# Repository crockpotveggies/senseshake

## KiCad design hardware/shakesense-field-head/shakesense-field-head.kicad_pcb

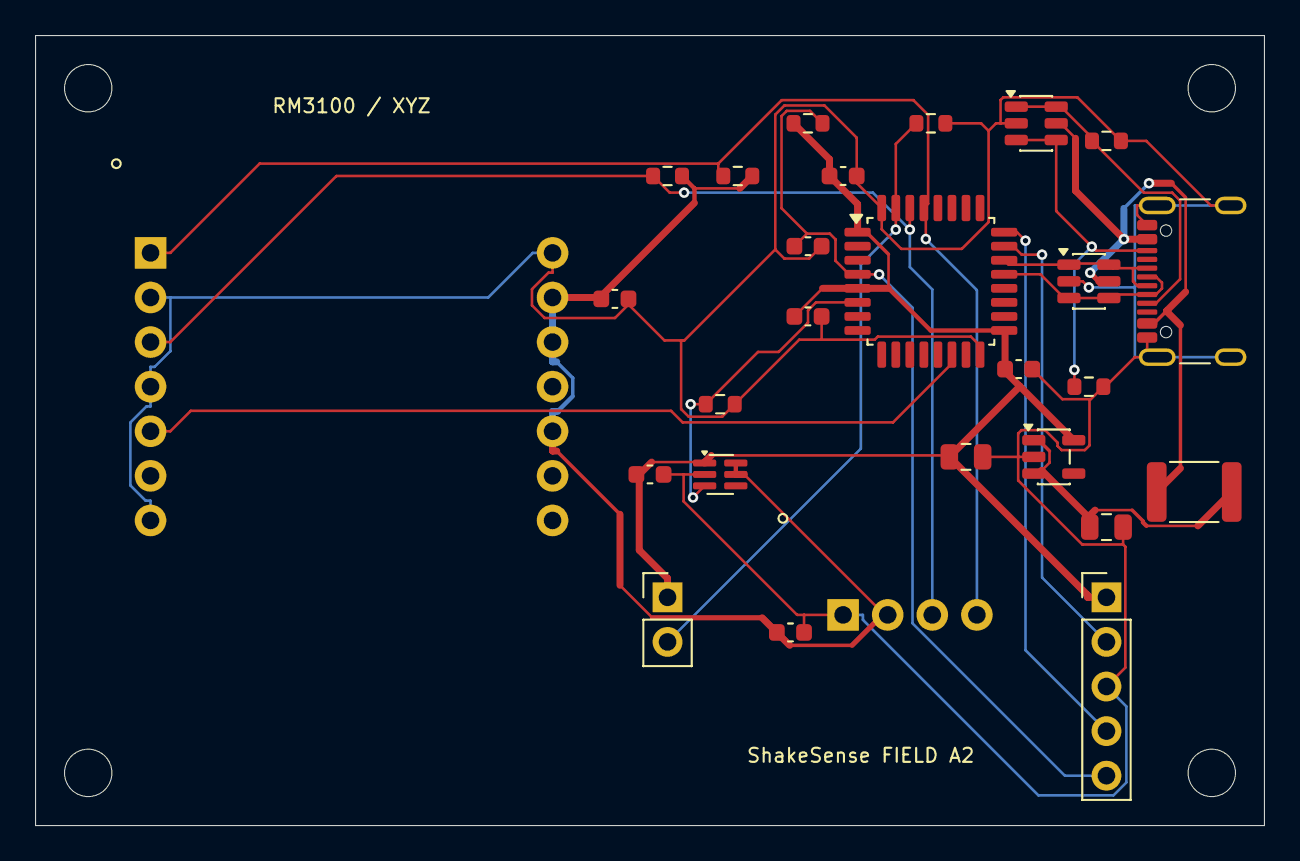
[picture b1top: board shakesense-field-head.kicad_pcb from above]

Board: 4 copper layers, 70.0 x 45.0 mm, 31 parts (0 on the bottom side), 17 nets.

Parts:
C1: 2.2u; Capacitor_SMD__C_0805_2012Metric
C2: 4.7u; Capacitor_SMD__C_0805_2012Metric
C3, C4, C5, C6, C7, C8, C9: 100n; Capacitor_SMD__C_0603_1608Metric
D1, D2: USBLC6-2SC6; Package_TO_SOT_SMD__SOT-23-6
F1: 500mA PTC; Fuse__Fuse_1812_4532Metric
H1, H2, H3, H4: M2.5 NPTH; MountingHole__MountingHole_2.7mm_M2.5
J1: USB-C DEVICE; Connector_USB__USB_C_Receptacle_GCT_USB4105-xx-A_16P_TopMnt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
J2: SWD / 3V3 SENSE; Connector_PinHeader_2.54mm__PinHeader_1x05_P2.54mm_Vertical
J3: BOOT0 jumper; Connector_PinHeader_2.54mm__PinHeader_1x02_P2.54mm_Vertical
R1, R2: 5.1k; Resistor_SMD__R_0603_1608Metric
R3, R4: 10k; Resistor_SMD__R_0603_1608Metric
R5: 100k; Resistor_SMD__R_0603_1608Metric
R7, R8: 4.7k; Resistor_SMD__R_0603_1608Metric
U1: STM32F042K6T6; Package_QFP__LQFP-32_7x7mm_P0.8mm
U2: RM3100 XYZ; ShakeSense__PNI_14190_Module
U3: DLVR-F50D option; ShakeSense__DLVR_E1BS
U4: AP2112K-3.3; Package_TO_SOT_SMD__SOT-23-5
U5: TPS22919; Package_TO_SOT_SMD__SOT-363_SC-70-6

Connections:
BOOT0: J3.2, R4.1, U1.31
GND: C1.2, C2.2, C3.2, C4.2, C5.2, C6.2, C7.2, C8.2, C9.2, D1.2, D2.2, J1.A1, J1.A12, J1.B1, J1.B12, J1.S1, J2.3, R1.2, R2.2, R4.2, R5.2, U1.16, U1.32, U2.2, U2.4, U2.7, U2.14, U3.1, U4.2, U5.2
MAG_DRDY: U1.14, U2.5
NRST: C8.1, J2.5, R3.2, U1.4
SCL: R8.1, U1.29, U2.1, U3.4
SDA: R7.1, U1.30, U2.3, U3.3
SENSOR_EN: R5.1, U1.6, U5.3
SWCLK: J2.4, U1.24
SWDIO: J2.2, U1.23
USB_5V: C1.1, F1.2, U4.1, U4.3
USB_CC1: D2.1, D2.6, J1.A5, R1.1
USB_CC2: D2.3, D2.4, J1.B5, R2.1
USB_DM: D1.3, D1.4, J1.A7, J1.B7, U1.21
USB_DP: D1.1, D1.6, J1.A6, J1.B6, U1.22
USB_VBUS: D1.5, D2.5, F1.1, J1.A4, J1.A9, J1.B4, J1.B9
V3: C2.1, C3.1, C6.1, C7.1, C9.1, J2.1, J3.1, R3.1, U1.1, U1.5, U1.17, U4.5, U5.1
V3_SENSOR: C4.1, C5.1, R7.2, R8.2, U2.10, U2.12, U2.13, U3.2, U5.5, U5.6

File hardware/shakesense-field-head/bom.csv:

Reference,Value,MPN,Footprint,DNP,Note
J1,USB-C DEVICE,USB4105-GF-A,Connector_USB__USB_C_Receptacle_GCT_USB4105-xx-A_16P_TopMnt_Horizontal,False,
R1,5.1k,RC0603FR-075K1L,Resistor_SMD__R_0603_1608Metric,False,
R2,5.1k,RC0603FR-075K1L,Resistor_SMD__R_0603_1608Metric,False,
D1,USBLC6-2SC6,USBLC6-2SC6,Package_TO_SOT_SMD__SOT-23-6,False,
D2,USBLC6-2SC6,USBLC6-2SC6,Package_TO_SOT_SMD__SOT-23-6,False,
F1,500mA PTC,MF-MSMF050-2,Fuse__Fuse_1812_4532Metric,False,
U4,AP2112K-3.3,AP2112K-3.3TRG1,Package_TO_SOT_SMD__SOT-23-5,False,
C1,2.2u,GRM21BR71E225KA73L,Capacitor_SMD__C_0805_2012Metric,False,
C2,4.7u,GRM21BR71A475KA73L,Capacitor_SMD__C_0805_2012Metric,False,
U1,STM32F042K6T6,STM32F042K6T6,Package_QFP__LQFP-32_7x7mm_P0.8mm,False,
C3,100n,GRM188R71H104KA93D,Capacitor_SMD__C_0603_1608Metric,False,
C6,100n,GRM188R71H104KA93D,Capacitor_SMD__C_0603_1608Metric,False,
C7,100n,GRM188R71H104KA93D,Capacitor_SMD__C_0603_1608Metric,False,
C8,100n,GRM188R71H104KA93D,Capacitor_SMD__C_0603_1608Metric,False,
R3,10k,RC0603FR-0710KL,Resistor_SMD__R_0603_1608Metric,False,
R4,10k,RC0603FR-0710KL,Resistor_SMD__R_0603_1608Metric,False,
J2,SWD / 3V3 SENSE,M20-9990545,Connector_PinHeader_2.54mm__PinHeader_1x05_P2.54mm_Vertical,False,Pin 1 is target voltage sense; do not externally power the rail
J3,BOOT0 jumper,EEPROM write enable,Connector_PinHeader_2.54mm__PinHeader_1x02_P2.54mm_Vertical,False,
U5,TPS22919,TPS22919DCKR,Package_TO_SOT_SMD__SOT-363_SC-70-6,False,
R5,100k,RC0603FR-07100KL,Resistor_SMD__R_0603_1608Metric,False,
C9,100n,GRM188R71H104KA93D,Capacitor_SMD__C_0603_1608Metric,False,
R7,4.7k,RC0603FR-074K7L,Resistor_SMD__R_0603_1608Metric,False,
R8,4.7k,RC0603FR-074K7L,Resistor_SMD__R_0603_1608Metric,False,
U2,RM3100 XYZ,PNI 14190,ShakeSense__PNI_14190_Module,False,
C4,100n,GRM188R71H104KA93D,Capacitor_SMD__C_0603_1608Metric,False,
U3,DLVR-F50D option,DLVR-F50D-E1BS-I-NI3F,ShakeSense__DLVR_E1BS,True,
C5,100n,GRM188R71H104KA93D,Capacitor_SMD__C_0603_1608Metric,False,
H1,M2.5 NPTH,M2.5 NPTH,MountingHole__MountingHole_2.7mm_M2.5,False,
H2,M2.5 NPTH,M2.5 NPTH,MountingHole__MountingHole_2.7mm_M2.5,False,
H3,M2.5 NPTH,M2.5 NPTH,MountingHole__MountingHole_2.7mm_M2.5,False,
H4,M2.5 NPTH,M2.5 NPTH,MountingHole__MountingHole_2.7mm_M2.5,False,

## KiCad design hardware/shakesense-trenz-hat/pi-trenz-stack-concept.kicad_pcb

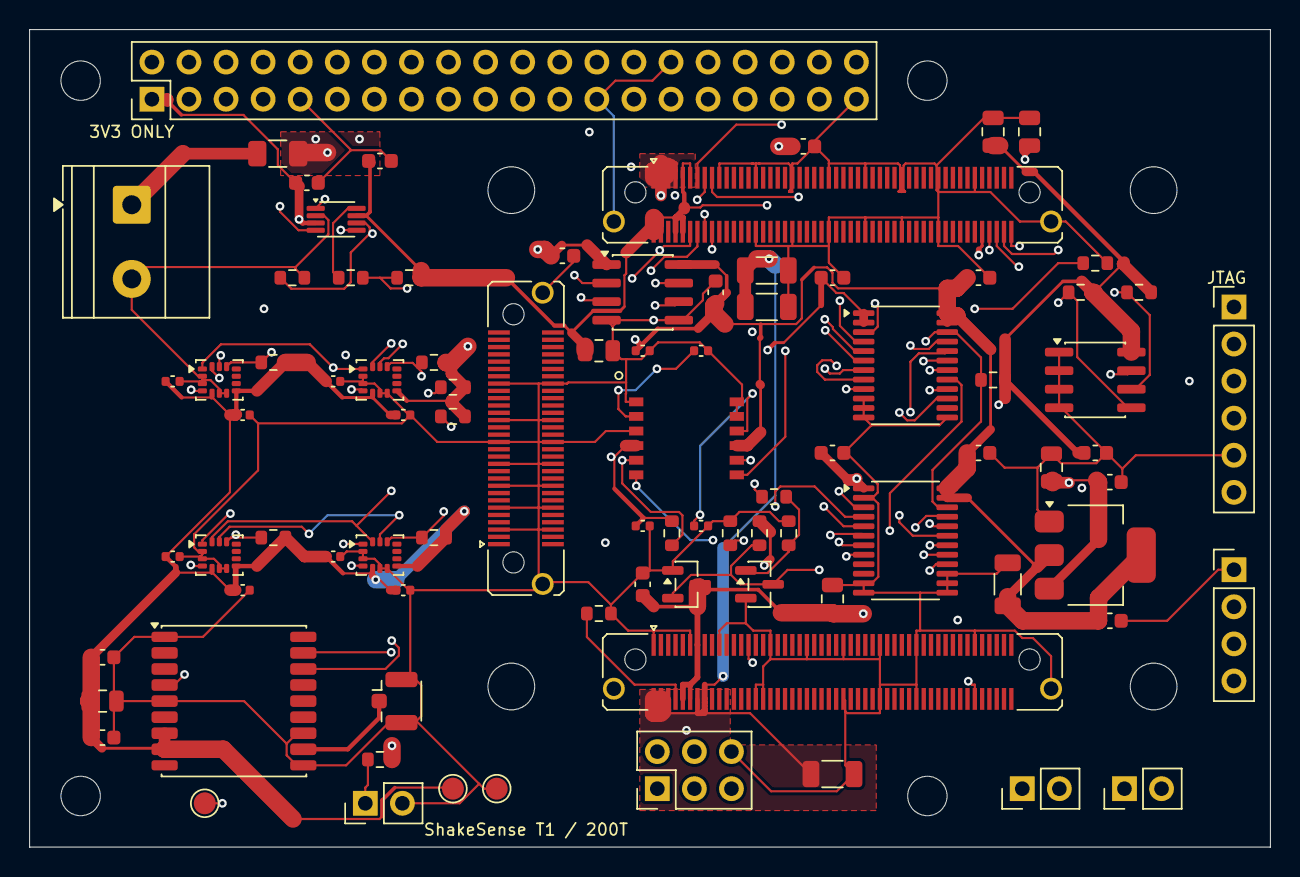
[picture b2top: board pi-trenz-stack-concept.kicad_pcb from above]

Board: 6 copper layers, 85.0 x 56.0 mm, 98 parts (0 on the bottom side), 64 nets.

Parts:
C1, C24, C26, C41, C43, C44, C45, C46, C47, C48, C49, C75, C76, C77, C83: 100n; Capacitor_SMD__C_0603_1608Metric
C2, C3, C40: 10u; Capacitor_SMD__C_0805_2012Metric
C12, C13, C14, C15, C16, C17, C18, C19, C20, C21, C22, C23: 100n; Capacitor_SMD__C_0402_1005Metric
C25, C84, C85: 4.7u; Capacitor_SMD__C_0805_2012Metric
C42, C80, C81, C82: 22u; Capacitor_SMD__C_1206_3216Metric
F80: 0467005.NR; TZ_TZ_FUSE
H1, H2, H3, H4: M2.5 NPTH; MountingHole__MountingHole_2.7mm_M2.5
H80, H81, H82, H83: M3 / 8 mm spacer; TZ_TZ_HOLE
J1: Raspberry Pi 40-pin; Connector_PinHeader_2.54mm__PinHeader_2x20_P2.54mm_Vertical
J2: Passive GNSS antenna; Connector_Coaxial__U.FL_Hirose_U.FL-R-SMT-1_Vertical
J4: FPGA test UART/reset; Connector_PinHeader_2.54mm__PinHeader_1x04_P2.54mm_Vertical
J80, J81: LSHM-150-04.0-L-DV-A-S-K-TR; TZ_TZ100
J82: LSHM-130-04.0-L-DV-A-S-K-TR; TZ_TZ60
J83: 1715721; TZ_TZ_POWER
J84: TSW-106-07-G-S; TZ_TZ_JTAG
J85: TSW-103-07-G-D; TZ_TZ_AUX
JP1: EEPROM write enable; Connector_PinHeader_2.54mm__PinHeader_1x02_P2.54mm_Vertical
JP80, JP81: TSW-102-07-G-S; TZ_TZ_JP
MODEL_PI4: Visualization only
MODEL_SPACERS: Visualization only
MODEL_TE0712: Visualization only
Q1: 2N7002; Package_TO_SOT_SMD__SOT-23
R1, R2: 3.9k; Resistor_SMD__R_0603_1608Metric
R3, R65: 1k; Resistor_SMD__R_0603_1608Metric
R11, R12, R13, R14, R20, R50, R63, R64, R80, R81: 10k; Resistor_SMD__R_0603_1608Metric
R51, R62, R66: 100k; Resistor_SMD__R_0603_1608Metric
R52, R53: 4.7k; Resistor_SMD__R_0603_1608Metric
R61: 47; Resistor_SMD__R_0603_1608Metric
TP1: SENS_3V3; TestPoint__TestPoint_Pad_D1.5mm
TP2: GND; TestPoint__TestPoint_Pad_D1.5mm
TP4: SENSOR_OE_N; TestPoint__TestPoint_Pad_D1.5mm
U1: 24LC32A; Package_SO__SOIC-8_3.9x4.9mm_P1.27mm
U11, U12, U13, U14: LSM6DSOTR; Package_LGA__LGA-14_3x2.5mm_P0.5mm_LayoutBorder3x4y
U20: SCL3300-D01; ShakeSense__SCL3300_D01
U21: MAX-M10S; RF_GPS__ublox_MAX
U40: TLV1117LV33DCYR; Package_TO_SOT_SMD__SOT-223-3_TabPin2
U41, U42: SN74LVC8T245PWR; Package_SO__TSSOP-24_4.4x7.8mm_P0.65mm
U43: ISO1640BDR; Package_SO__SOIC-8_3.9x4.9mm_P1.27mm
U51: TXU0202DCUR; Package_SO__VSSOP-8_2.3x2mm_P0.5mm
U52: TLV803EA30DBZR; Package_TO_SOT_SMD__SOT-23

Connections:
EEP_WP: JP1.1, R3.1, U1.7
EXT_3V3: F80.1, J83.1
FPGA_3V3: C76.1, C77.1, C84.1, C85.1, J80.10, J80.12, J80.13, J81.2, J81.4, J81.8, J81.9, J81.10, J81.11, J81.92, J84.6, R63.2, R64.2, U51.7, U52.3
FPGA_AUX0: J81.15, J85.1
FPGA_AUX1: J81.16, J85.3
FPGA_AUX2: J81.18, J85.5
FPGA_CONFIG_RESET_N: J81.17, JP81.1
FPGA_EN1: J80.27, JP80.1
FPGA_IO_ENABLE: J1.22, R62.1, U51.6
FPGA_JTAGEN: J80.90, R80.1
FPGA_NOSEQ: J80.8, R81.1
FPGA_RESET_GATE: Q1.1, R65.2, R66.1
FPGA_RESET_GPIO: J1.11, R65.1
FPGA_RESET_N: J4.4, J81.13, Q1.3, R64.1, U52.2
FPGA_UART_DRIVE: R61.1, U51.8
FPGA_UART_RX: J4.2, J81.12, R61.2, R63.1
FPGA_UART_TX: J4.3, J81.14, U51.1
FPGA_VIN: C80.1, C81.1, C82.1, C83.1, F80.2, J80.2, J80.4, J80.6, J80.14, J80.16, J81.1, J81.3, J81.5, J81.7
GND: C1.2, C2.2, C3.2, C12.2, C13.2, C14.2, C15.2, C16.2, C17.2, C18.2, C19.2, C20.2, C21.2, C22.2, C23.2, C24.2, C25.2, C26.2, C40.2, C41.2, C42.2, C43.2, C44.2, C45.2, C46.2, C47.2, C48.2, C49.2, C75.2, C76.2, C77.2, C80.2, C81.2, C82.2, C83.2, C84.2, C85.2, J1.6, J1.9, J1.14, J1.20, J1.25, J1.30, J1.34, J1.39, J2.2, J4.1, J80.1, J80.11, J80.19, J80.30, J80.32, J80.33, J80.43, J80.53, J80.54, J80.63, J80.64, J80.73, J80.74, J80.89, J80.101, J81.19, J81.29, J81.30, J81.39, J81.40, J81.49, J81.50, J81.59, J81.60, J81.69, J81.70, J81.79, J81.80, J81.89, J81.101, J82.5, J82.6, J82.11, J82.12, J82.17, J82.18, J82.23, J82.24, J82.29, J82.30, J82.35, J82.36, J82.45, J82.46, J82.61, J83.2, J84.5, J85.2, J85.4, J85.6, JP1.2, JP80.2, JP81.2, Q1.2, R51.2, R62.2, R66.2, R80.2, R81.2, TP2.1, U1.1, U1.2, U1.3, U1.4, U11.2, U11.3, U11.6, U11.7, U12.2, U12.3, U12.6, U12.7, U13.2, U13.3, U13.6, U13.7, U14.2, U14.3, U14.6, U14.7, U20.1, U20.3, U20.11, U20.12, U21.1, U21.5, U21.10, U21.12, U40.1, U41.10, U41.11, U41.12, U41.13, U42.2, U42.11, U42.12, U42.13, U42.14, U42.15, U43.4, U43.5, U51.2, U52.1
GNSS_PPS: U21.4, U42.16
GNSS_RF: J2.1, U21.11
I2C_SCL: R53.1, U21.17, U43.6
I2C_SDA: R52.1, U21.16, U43.7
ID_SCL: J1.28, R2.1, U1.6
ID_SDA: J1.27, R1.1, U1.5
IMU1_CS: R11.1, U11.12, U41.19
IMU1_INT: U11.4, U42.20
IMU2_CS: R12.1, U12.12, U41.18
IMU2_INT: U12.4, U42.19
IMU3_CS: R13.1, U13.12, U41.17
IMU3_INT: U13.4, U42.18
IMU4_CS: R14.1, U14.12, U41.16
IMU4_INT: U14.4, U42.17
JTAG_TCK: J81.100, J84.4
JTAG_TDI: J81.96, J84.2
JTAG_TDO: J81.98, J84.3
JTAG_TMS: J81.94, J84.1
PI_3V3: C1.1, C2.1, C44.1, C46.1, C48.1, C75.1, J1.1, J1.17, R1.2, R2.2, R3.2, R50.2, U1.8, U41.1, U41.2, U42.1, U43.1, U51.3
PI_5V: C3.1, C40.1, C41.1, J1.2, J1.4, U40.3
PI_GNSS_PPS: J1.7, U42.8
PI_I2C_SCL: J1.5, U43.3
PI_I2C_SDA: J1.3, U43.2
PI_IMU1_CS: J1.24, U41.5
PI_IMU1_INT: J1.13, U42.4
PI_IMU2_CS: J1.26, U41.6
PI_IMU2_INT: J1.15, U42.5
PI_IMU3_CS: J1.29, U41.7
PI_IMU3_INT: J1.16, U42.6
PI_IMU4_CS: J1.31, U41.8
PI_IMU4_INT: J1.18, U42.7
PI_SPI_MISO: J1.21, U42.3
PI_SPI_MOSI: J1.19, U41.3
PI_SPI_SCLK: J1.23, U41.4
PI_TILT_CS: J1.33, U41.9
PI_UART_RX: J1.10, U51.4
PI_UART_TX: J1.8, U51.5
SENSOR_OE_N: J1.37, R50.1, TP4.1, U41.22, U42.22
SENS_3V3: C12.1, C13.1, C14.1, C15.1, C16.1, C17.1, C18.1, C19.1, C20.1, C22.1, C24.1, C25.1, C26.1, C42.1, C43.1, C45.1, C47.1, C49.1, R11.2, R12.2, R13.2, R14.2, R20.2, R52.2, R53.2, TP1.1, U11.5, U11.8, U12.5, U12.8, U13.5, U13.8, U14.5, U14.8, U20.4, U20.9, U21.7, U21.8, U40.2, U41.23, U41.24, U42.23, U42.24, U43.8
SPI_MISO: R51.1, U11.1, U12.1, U13.1, U14.1, U20.6, U42.21
SPI_MOSI: U11.14, U12.14, U13.14, U14.14, U20.7, U41.21
SPI_SCLK: U11.13, U12.13, U13.13, U14.13, U20.8, U41.20
TILT_AEXT: C21.1, U20.2
TILT_CS: R20.1, U20.5, U41.15
TILT_DEXT: C23.1, U20.10
